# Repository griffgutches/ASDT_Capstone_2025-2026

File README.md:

# ASDT Datalogger
This PCB is a rocketry flight datalogger with a comprehensive sensor suite.

## Features
- GPS
- Radio
- IMU
- Barometer
- Magnetometer
- Status LEDs
- Reverse polarity protection

## Parts
- ESP32-S3 microcontroller
- u-blox MAX-M10S GPS
- RFM95W-915 radio (SX1276)
- ISM6HG256X High/Low-G IMU
- BMI088 Low-G IMU
- ADXL375 High-G IMU
- MS5607 barometer
- BMP390 barometer
- MMC5983MA magnetometer

## Pinout
| GPIO | Function            |
|------|---------------------|
|    0 | BOOT                |
|    1 | MS5607 Baro CS      |
|    2 | BMP390 Baro CS      |
|    4 | MMC598 Mag CS       |
|    7 | Radio CS            |
|   14 | BMI088 Gyro CS      |
|   21 | ADXL375 IMU CS      |
|   40 | BMI088 Accel CS     |
|   41 | ISM6HG256X IMU CS   |
|   11 | ADXL375 INT         |
|   13 | Radio INT           |
|   18 | BMI088 Accel INT    |
|   31 | GPS INT             |
|   42 | MMC598 Mag INT      |
|   10 | MISO                |
|   17 | SCK                 |
|   44 | MOSI                |
|   45 | SCL*                |
|   46 | SDA*                |
|   25 | Flash I03           |
|   26 | Flash I02           |
|   27 | Flash CS            |
|   28 | Flash CLK           |
|   29 | Flash IO1           |
|   30 | Flash IO0           |
|   35 | SD CMD              |
|   37 | SD data 0           |
|   38 | SD data 1           |
|   33 | SD data 2           |
|   34 | SD data 3           |
|   36 | SD clock            |
|   15 | XTAL_32K_P          |
|   16 | XTAL_32K_N          |
|   19 | USB_D-              |
|   20 | USB_D+              |
|    8 | Timepulse           |
|    9 | Battery Sense       |
|   39 | Buzzer              |
|   43 | ANT_SW              |
|    6 | Radio Busy          |

*SDA/SCL should be moved off GPIO45/46 on future designs because they are strapping pins

## Addresses
| Name             | Part     | I2C Address |
|------------------|----------|-------------|
| GPS              | MAX-M10S | 0x42 ****   |

## Notes
- The boot and reset button on the board are enabled by the jumper J5 on the left side of the board, this jumper must be removed before flight
- The radio **may be damaged** if it is run without an antenna attached
- The LED data pin should never be floating
- The battery sense pin is connected through a 300k-100k voltage divider, so the pin voltage is 0.25 times the battery voltage
- The total current consumption should be below 500mA continuous
- The GPS will blink an LED near the bottom of the board once per second once it gets a fix

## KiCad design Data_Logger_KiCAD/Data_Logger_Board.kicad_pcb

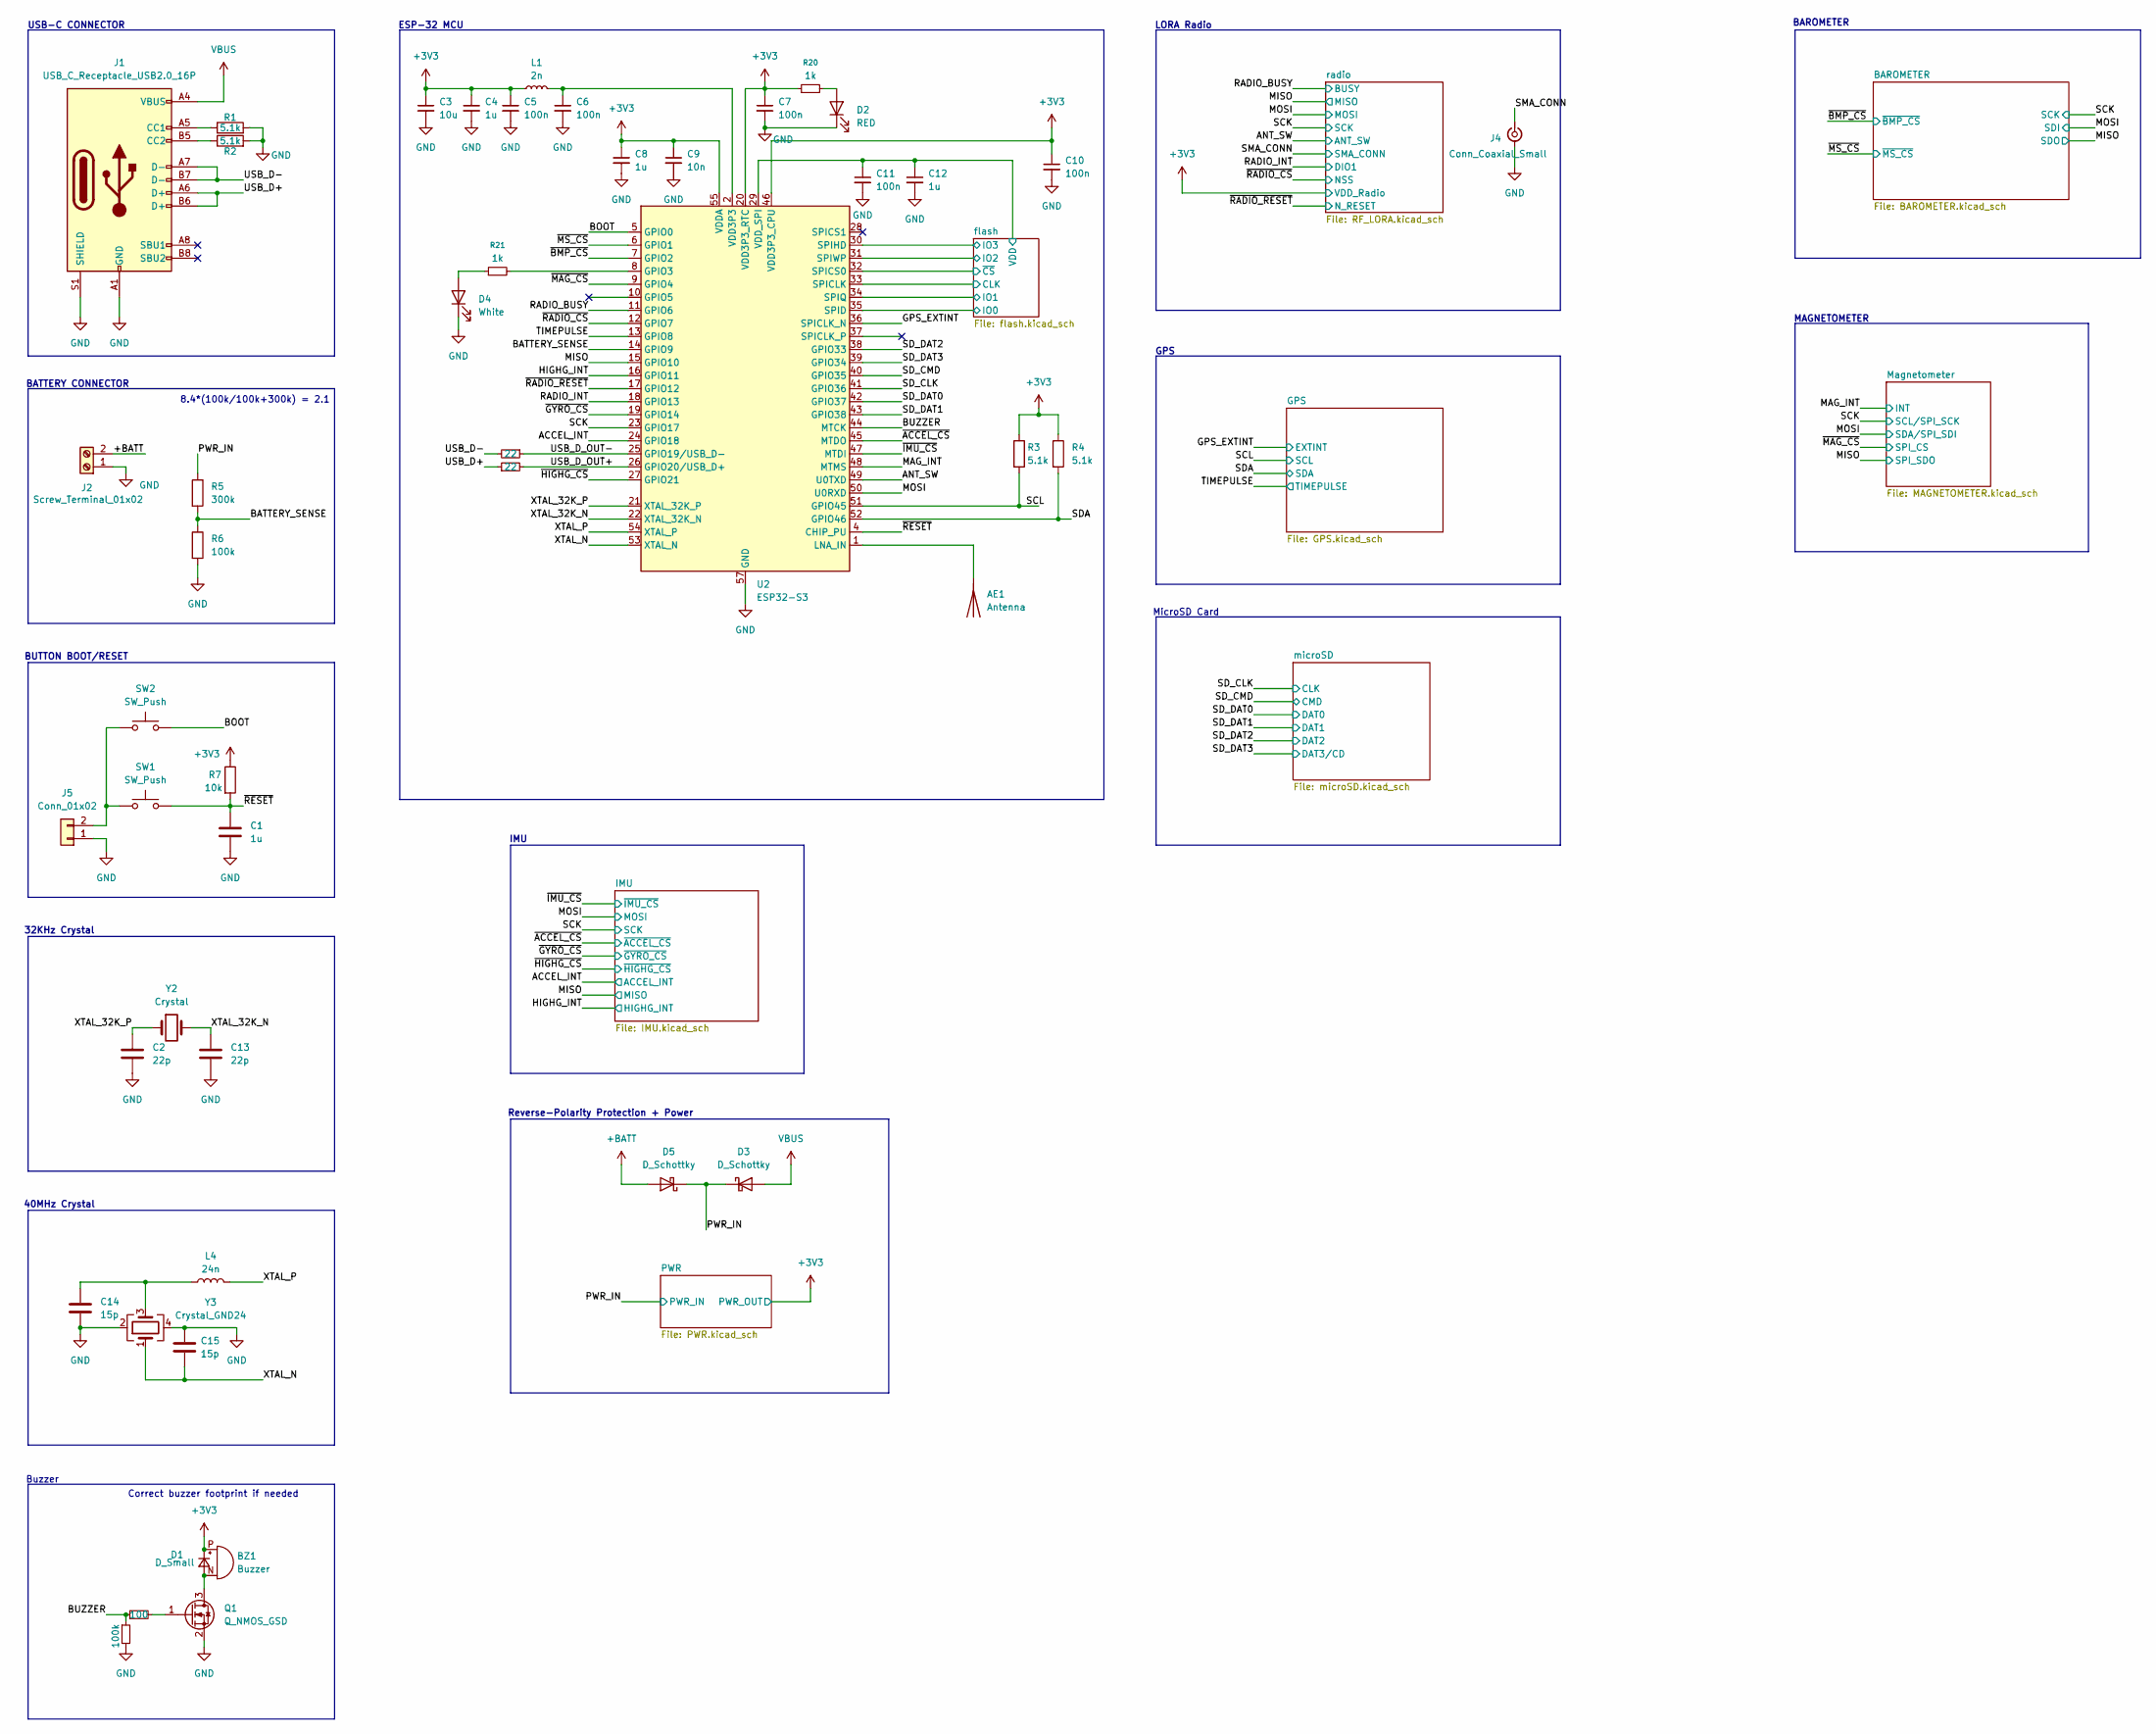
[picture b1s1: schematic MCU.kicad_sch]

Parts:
AE1: Antenna; Molex_47948-0001_2.4Ghz; LCSC C152351
BZ1: Buzzer; CUI_CMT-4023S-SMT-TR
C1, C4, C8, C12: 1u; C_0402_1005Metric; LCSC C52923
C2, C13: 22p; C_0402_1005Metric; LCSC C1555
C3: 10u; C_0603_1608Metric; LCSC C19702
C5, C6, C7, C10, C11: 100n; C_0402_1005Metric; LCSC C1525
C9: 10n; C_0402_1005Metric; LCSC C15195
C14, C15: 15p; C_0402_1005Metric; LCSC C1548
D1: D_Small; D_SOD-123F; LCSC C64898
D2: RED; LED_0603_1608Metric
D3, D5: D_Schottky; D_SOD-123; LCSC C8598
D4: White; LED_0603_1608Metric
J1: USB_C_Receptacle_USB2.0_16P; USB_C_Receptacle_G-Switch_GT-USB-7010ASV; LCSC C2988369
J2: Screw_Terminal_01x02; TerminalBlock_Xinya_XY308-2.54-2P_1x02_P2.54mm_Horizontal
J4: Conn_Coaxial_Small; SMA_Samtec_SMA-J-P-H-ST-EM1_EdgeMount
J5: Conn_01x02; PinHeader_1x02_P1.27mm_Vertical
L1: 2n; L_0402_1005Metric; LCSC C18216
L4: 24n; L_0402_1005Metric; LCSC C74301
Q1: Q_NMOS_GSD; SOT-23; LCSC C28646273
R1, R2, R3, R4: 5.1k; R_0402_1005Metric; LCSC C25905
R5: 300k; R_0402_1005Metric; LCSC C25774
R6, R14: 100k; R_0402_1005Metric; LCSC C25741
R7: 10k; R_0402_1005Metric; LCSC C25744
R11, R12: 22; R_0402_1005Metric; LCSC C25092
R13: 100; R_0402_1005Metric; LCSC C25076
R20, R21: 1k; R_0402_1005Metric; LCSC C11702
SW1, SW2: SW_Push; SW_SPST_TS-1088-xR020; LCSC C720477
U2: ESP32-S3; QFN-56-1EP_7x7mm_P0.4mm_EP4x4mm; LCSC C2913192
Y2: Crystal; Crystal_SMD_3215-2Pin_3.2x1.5mm; LCSC C32346
Y3: Crystal_GND24; Crystal_SMD_2016-4Pin_2.0x1.6mm; LCSC C501798

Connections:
+3V3: BZ1.P (+), C3.1, C4.1, C5.1, C7.1, C8.1, C9.1, C10.1, D1.1 (K), L1.1, R3.1, R4.1, R7.1, R20.1, U2.20 (VDD3P3_RTC), U2.46 (VDD3P3_CPU), U2.55 (VDDA), U2.56 (VDDA); also elsewhere on the board
+BATT: D5.2 (A), J2.2
/MCU/ACCEL_INT: U2.24 (GPIO18); also elsewhere on the board
/MCU/ANT_SW: U2.49 (U0TXD); also elsewhere on the board
/MCU/BATTERY_SENSE: R5.2, R6.1, U2.14 (GPIO9)
/MCU/BOOT: SW2.2, U2.5 (GPIO0)
/MCU/BUZZER: R13.1, R14.1, U2.44 (MTCK)
/MCU/GPS_EXTINT: U2.36 (SPICLK_N); also elsewhere on the board
/MCU/HIGHG_INT: U2.16 (GPIO11); also elsewhere on the board
/MCU/MAG_INT: U2.48 (MTMS); also elsewhere on the board
/MCU/MISO: U2.15 (GPIO10); also elsewhere on the board
/MCU/MOSI: U2.50 (U0RXD); also elsewhere on the board
/MCU/PWR_IN: D3.1 (K), D5.1 (K), R5.1; also elsewhere on the board
/MCU/RADIO_BUSY: U2.11 (GPIO6); also elsewhere on the board
/MCU/RADIO_INT: U2.18 (GPIO13); also elsewhere on the board
/MCU/SCK: U2.23 (GPIO17); also elsewhere on the board
/MCU/SCL: R3.2, U2.51 (GPIO45); also elsewhere on the board
/MCU/SDA: R4.2, U2.52 (GPIO46); also elsewhere on the board
/MCU/SD_CLK: U2.41 (GPIO36); also elsewhere on the board
/MCU/SD_CMD: U2.40 (GPIO35); also elsewhere on the board
/MCU/SD_DAT0: U2.42 (GPIO37); also elsewhere on the board
/MCU/SD_DAT1: U2.43 (GPIO38); also elsewhere on the board
/MCU/SD_DAT2: U2.38 (GPIO33); also elsewhere on the board
/MCU/SD_DAT3: U2.39 (GPIO34); also elsewhere on the board
/MCU/SMA_CONN: J4.1 (In); also elsewhere on the board
/MCU/TIMEPULSE: U2.13 (GPIO8); also elsewhere on the board
/MCU/USB_D+: J1.A6 (D+), J1.B6 (D+), R12.1
/MCU/USB_D-: J1.A7 (D-), J1.B7 (D-), R11.2
/MCU/USB_D_OUT+: R12.2, U2.26 (GPIO20/USB_D+)
/MCU/USB_D_OUT-: R11.1, U2.25 (GPIO19/USB_D-)
/MCU/XTAL_32K_N: C13.1, U2.22 (XTAL_32K_N), Y2.2
/MCU/XTAL_32K_P: C2.1, U2.21 (XTAL_32K_P), Y2.1
/MCU/XTAL_N: C15.2, U2.53 (XTAL_N), Y3.1
/MCU/XTAL_P: L4.2, U2.54 (XTAL_P)
/MCU/flash/CLK: U2.33 (SPICLK); also elsewhere on the board
/MCU/flash/IO0: U2.35 (SPID); also elsewhere on the board
/MCU/flash/IO1: U2.34 (SPIQ); also elsewhere on the board
/MCU/flash/IO2: U2.31 (SPIWP); also elsewhere on the board
/MCU/flash/IO3: U2.30 (SPIHD); also elsewhere on the board
/MCU/flash/VDD: C11.1, C12.1, U2.29 (VDD_SPI); also elsewhere on the board
/MCU/flash/~CS: U2.32 (SPICS0); also elsewhere on the board
/MCU/~ACCEL_CS: U2.45 (MTDO); also elsewhere on the board
/MCU/~BMP_CS: U2.7 (GPIO2); also elsewhere on the board
/MCU/~GYRO_CS: U2.19 (GPIO14); also elsewhere on the board
/MCU/~HIGHG_CS: U2.27 (GPIO21); also elsewhere on the board
/MCU/~IMU_CS: U2.47 (MTDI); also elsewhere on the board
/MCU/~MAG_CS: U2.9 (GPIO4); also elsewhere on the board
/MCU/~MS_CS: U2.6 (GPIO1); also elsewhere on the board
/MCU/~RADIO_CS: U2.12 (GPIO7); also elsewhere on the board
/MCU/~RADIO_RESET: U2.17 (GPIO12); also elsewhere on the board
/MCU/~RESET: C1.1, R7.2, SW1.2, U2.4 (CHIP_PU)
GND: C1.2, C2.2, C3.2, C4.2, C5.2, C6.2, C7.2, C8.2, C9.2, C10.2, C11.2, C12.2, C13.2, C14.2, C15.1, D2.1 (K), D4.1 (K), J1.A1 (GND), J1.A12 (GND), J1.B1 (GND), J1.B12 (GND), J1.S1 (SHIELD), J2.1, J4.2 (Ext), J5.1, Q1.2 (S), R1.2, R2.2, R6.2, R14.2, U2.57 (GND), Y3.2, Y3.4; also elsewhere on the board
unnamed: AE1.1 (A), U2.1 (LNA_IN)
unnamed: BZ1.N (-), D1.2 (A), Q1.3 (D)
unnamed: C6.1, L1.2, U2.2 (VDD3P3), U2.3 (VDD3P3)
unnamed: C14.1, L4.1, Y3.3
unnamed: D2.2 (A), R20.2
unnamed: D4.2 (A), R21.1
unnamed: J1.A5 (CC1), R1.1
unnamed: J1.B5 (CC2), R2.1
unnamed: J5.2, SW1.1, SW2.1
unnamed: Q1.1 (G), R13.2
unnamed: R21.2, U2.8 (GPIO3)
VBUS: D3.2 (A), J1.A4 (VBUS), J1.A9 (VBUS), J1.B4 (VBUS), J1.B9 (VBUS)

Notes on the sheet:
ESP-32 MCU
Correct buzzer footprint if needed
Buzzer
MAGNETOMETER
Reverse-Polarity Protection + Power
IMU
BATTERY CONNECTOR
BUTTON BOOT/RESET
MicroSD Card
8.4*(100k/100k+300k) = 2.1
32KHz Crystal
40MHz Crystal
BAROMETER
LORA Radio
GPS
USB-C CONNECTOR

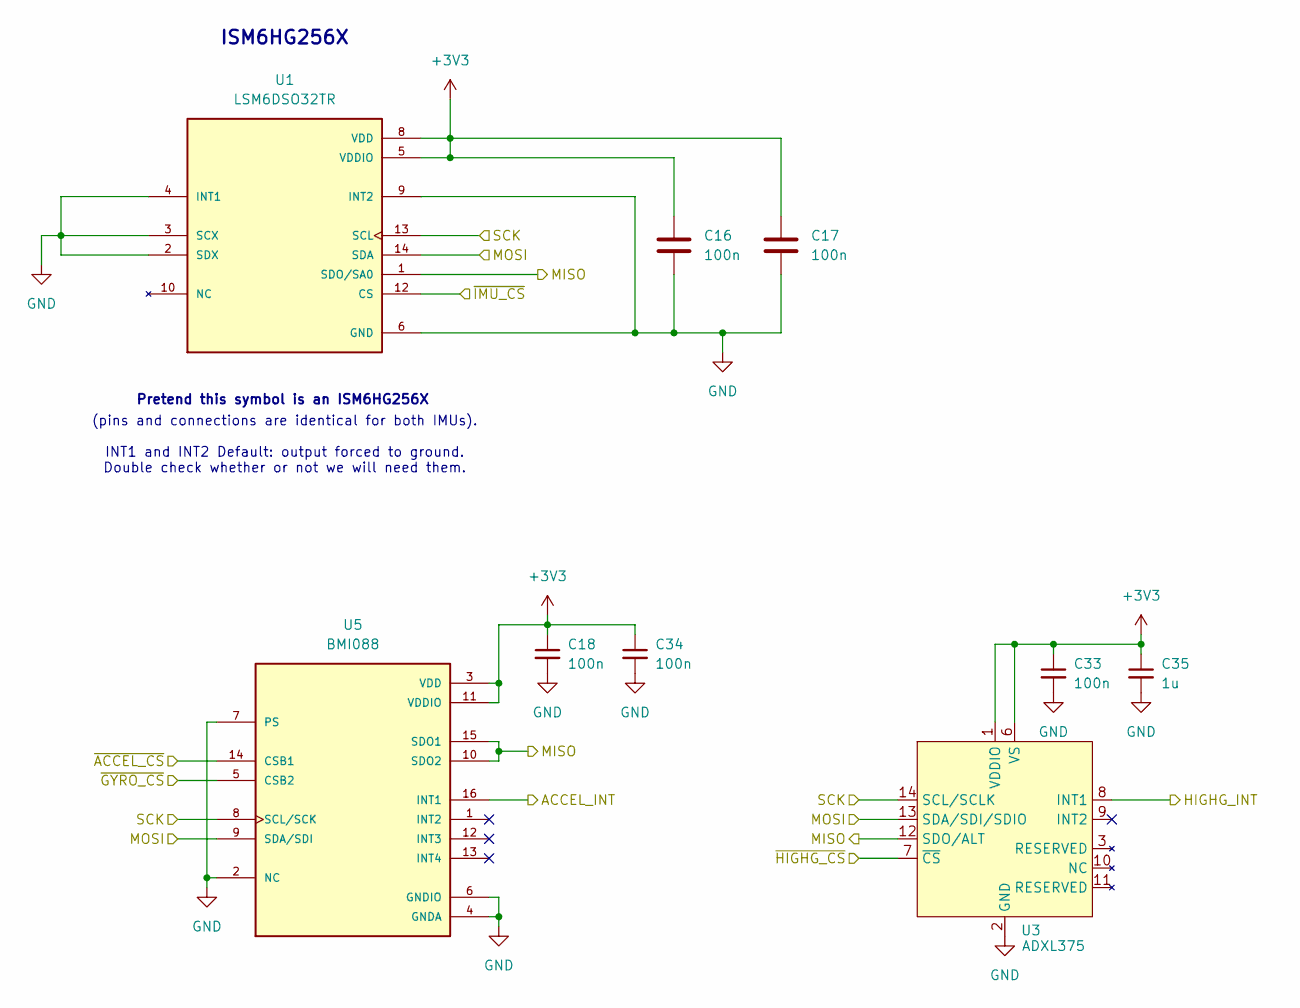
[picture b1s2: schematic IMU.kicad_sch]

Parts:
C16, C17, C18, C33, C34: 100n; C_0402_1005Metric; LCSC C1525
C35: 1u; C_0402_1005Metric; LCSC C52923
U1: LSM6DSO32TR; LGA-14_3x2.5mm_P0.5mm_LayoutBorder3x4y; PARTREV 1
U3: ADXL375; LGA_CC-14-1_ADI; digikey ADXL375BCCZ-RL7CT-ND
U5: BMI088; PQFN50P450X300X100-16N

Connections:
+3V3: C16.1, C17.1, C18.1, C33.1, C34.1, C35.1, U1.5 (VDDIO), U1.8 (VDD), U3.1 (VDDIO), U3.6 (VS), U5.3 (VDD), U5.11 (VDDIO); also elsewhere on the board
/MCU/ACCEL_INT: U5.16 (INT1); also elsewhere on the board
/MCU/HIGHG_INT: U3.8 (INT1); also elsewhere on the board
/MCU/MISO: U1.1 (SDO/SA0), U3.12 (SDO/ALT), U5.10 (SDO2), U5.15 (SDO1); also elsewhere on the board
/MCU/MOSI: U1.14 (SDA), U3.13 (SDA/SDI/SDIO), U5.9 (SDA/SDI); also elsewhere on the board
/MCU/SCK: U1.13 (SCL), U3.14 (SCL/SCLK), U5.8 (SCL/SCK); also elsewhere on the board
/MCU/~ACCEL_CS: U5.14 (CSB1); also elsewhere on the board
/MCU/~GYRO_CS: U5.5 (CSB2); also elsewhere on the board
/MCU/~HIGHG_CS: U3.7 (~CS); also elsewhere on the board
/MCU/~IMU_CS: U1.12 (CS); also elsewhere on the board
GND: C16.2, C17.2, C18.2, C33.2, C34.2, C35.2, U1.2 (SDX), U1.3 (SCX), U1.4 (INT1), U1.6 (GND), U1.7 (GND), U1.9 (INT2), U3.2 (GND), U3.4 (GND), U3.5 (GND), U5.2 (NC), U5.4 (GNDA), U5.6 (GNDIO), U5.7 (PS); also elsewhere on the board

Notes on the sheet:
Pretend this symbol is an ISM6HG256X
ISM6HG256X
(pins and connections are identical for both IMUs). INT1 and INT2 Default: output forced to ground. Double check whether or not we will need them.

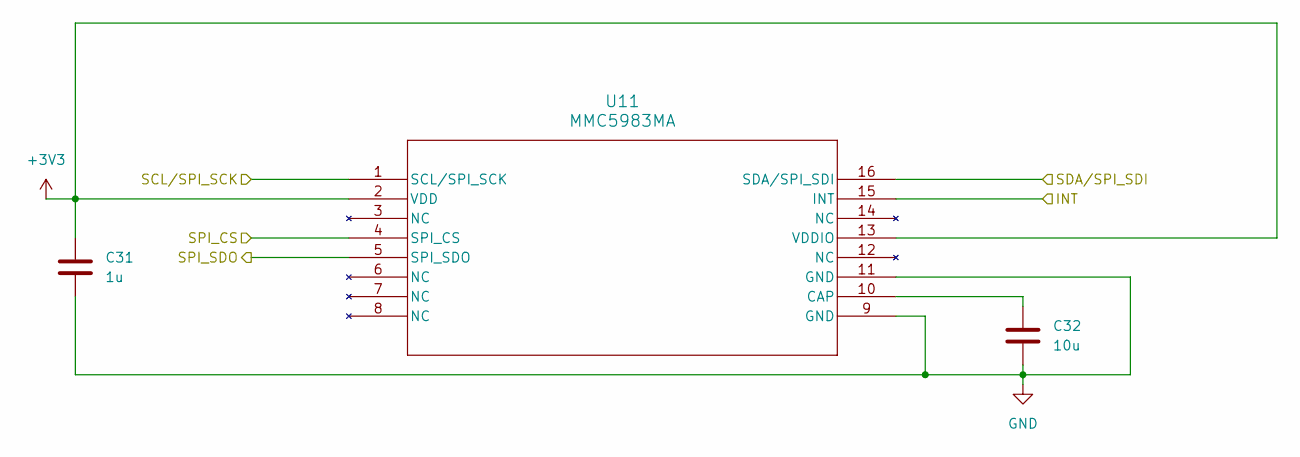
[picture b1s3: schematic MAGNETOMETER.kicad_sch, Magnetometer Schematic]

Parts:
C31: 1u; C_0402_1005Metric; LCSC C52923
C32: 10u; C_0402_1005Metric; LCSC C15525
U11: MMC5983MA; LGA-16_3x3mm_P0.5mm_LayoutBorder3x5y

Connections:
+3V3: C31.1, U11.2 (VDD), U11.13 (VDDIO); also elsewhere on the board
/MCU/MAG_INT: U11.15 (INT); also elsewhere on the board
/MCU/MISO: U11.5 (SPI_SDO); also elsewhere on the board
/MCU/MOSI: U11.16 (SDA/SPI_SDI); also elsewhere on the board
/MCU/SCK: U11.1 (SCL/SPI_SCK); also elsewhere on the board
/MCU/~MAG_CS: U11.4 (SPI_CS); also elsewhere on the board
GND: C31.2, C32.2, U11.9 (GND), U11.11 (GND); also elsewhere on the board
unnamed: C32.1, U11.10 (CAP)

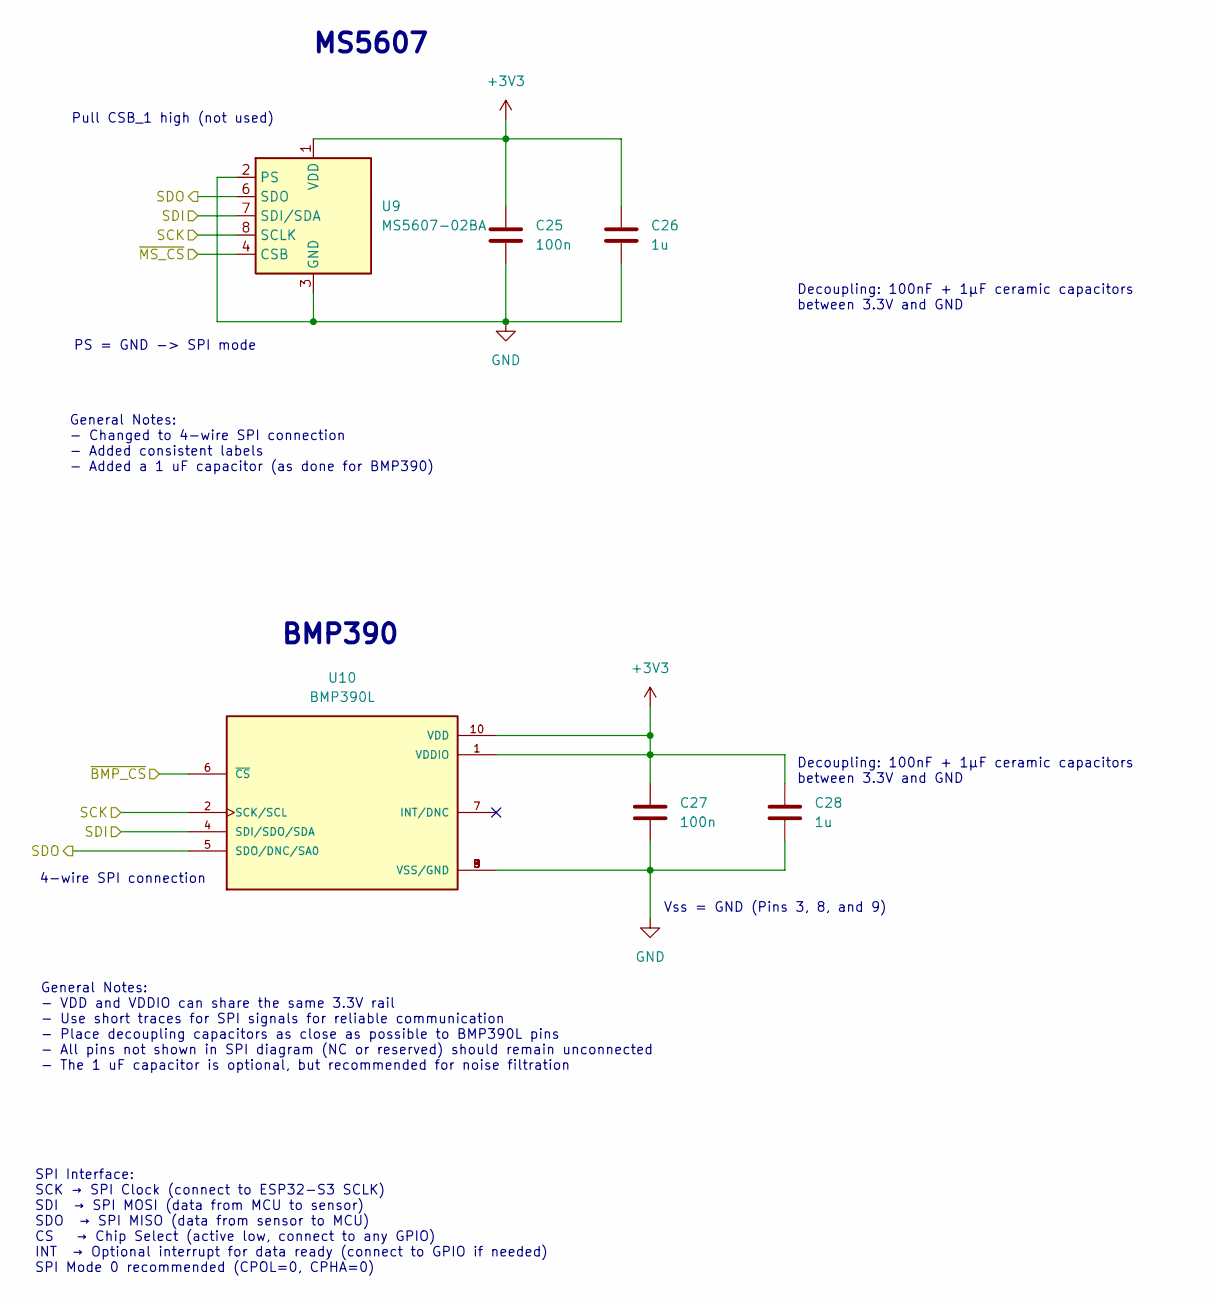
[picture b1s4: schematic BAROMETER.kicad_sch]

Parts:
C25, C27: 100n; C_0402_1005Metric; LCSC C1525
C26, C28: 1u; C_0402_1005Metric; LCSC C52923
U9: MS5607-02BA; LGA-8_3x5mm_P1.25mm; LCSC C97627
U10: BMP390L; XDCR_BMP390L; PARTREV 1.7

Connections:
+3V3: C25.1, C26.2, C27.1, C28.1, U9.1 (VDD), U10.1 (VDDIO), U10.10 (VDD); also elsewhere on the board
/MCU/MISO: U9.6 (SDO), U10.5 (SDO/DNC/SA0); also elsewhere on the board
/MCU/MOSI: U9.7 (SDI/SDA), U10.4 (SDI/SDO/SDA); also elsewhere on the board
/MCU/SCK: U9.8 (SCLK), U10.2 (SCK/SCL); also elsewhere on the board
/MCU/~BMP_CS: U10.6 (~CS); also elsewhere on the board
/MCU/~MS_CS: U9.4 (CSB), U9.5 (CSB); also elsewhere on the board
GND: C25.2, C26.1, C27.2, C28.2, U9.2 (PS), U9.3 (GND), U10.3 (VSS/GND), U10.8 (VSS/GND), U10.9 (VSS/GND); also elsewhere on the board

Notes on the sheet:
4-wire SPI connection
Decoupling: 100nF + 1µF ceramic capacitors between 3.3V and GND
Vss = GND (Pins 3, 8, and 9)
MS5607
General Notes: - Changed to 4-wire SPI connection - Added consistent labels - Added a 1 uF capacitor (as done for BMP390)
BMP390
PS = GND -> SPI mode
Pull CSB_1 high (not used)
SPI Interface: SCK → SPI Clock (connect to ESP32-S3 SCLK) SDI → SPI MOSI (data from MCU to sensor) SDO → SPI MISO (data from sensor to MCU) CS → Chip Select (active low, connect to any GPIO) INT → Optional interrupt for data ready (connect to GPIO if needed) SPI Mode 0 recommended (CPOL=0, CPHA=0)
General Notes: - VDD and VDDIO can share the same 3.3V rail - Use short traces for SPI signals for reliable communication - Place decoupling capacitors as close as possible to BMP390L pins - All pins not shown in SPI diagram (NC or reserved) should remain unconnected - The 1 uF capacitor is optiona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

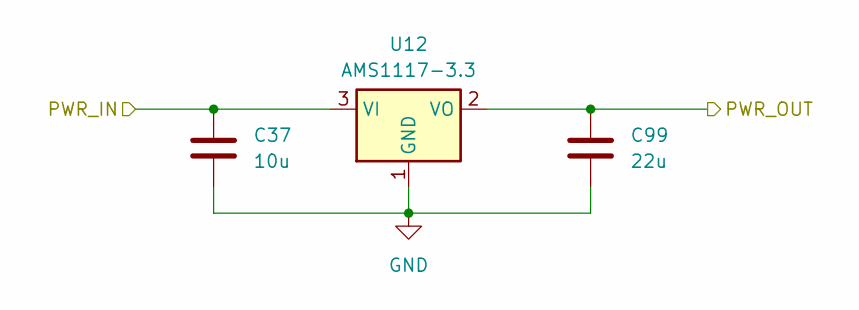
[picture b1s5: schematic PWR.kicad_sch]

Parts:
C37: 10u; C_0603_1608Metric; LCSC C19702
C99: 22u; C_0603_1608Metric; LCSC C59461
U12: AMS1117-3.3; SOT-223-3_TabPin2; LCSC C6186

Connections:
+3V3: C99.1, U12.2 (VO); also elsewhere on the board
/MCU/PWR_IN: C37.1, U12.3 (VI); also elsewhere on the board
GND: C37.2, C99.2, U12.1 (GND); also elsewhere on the board

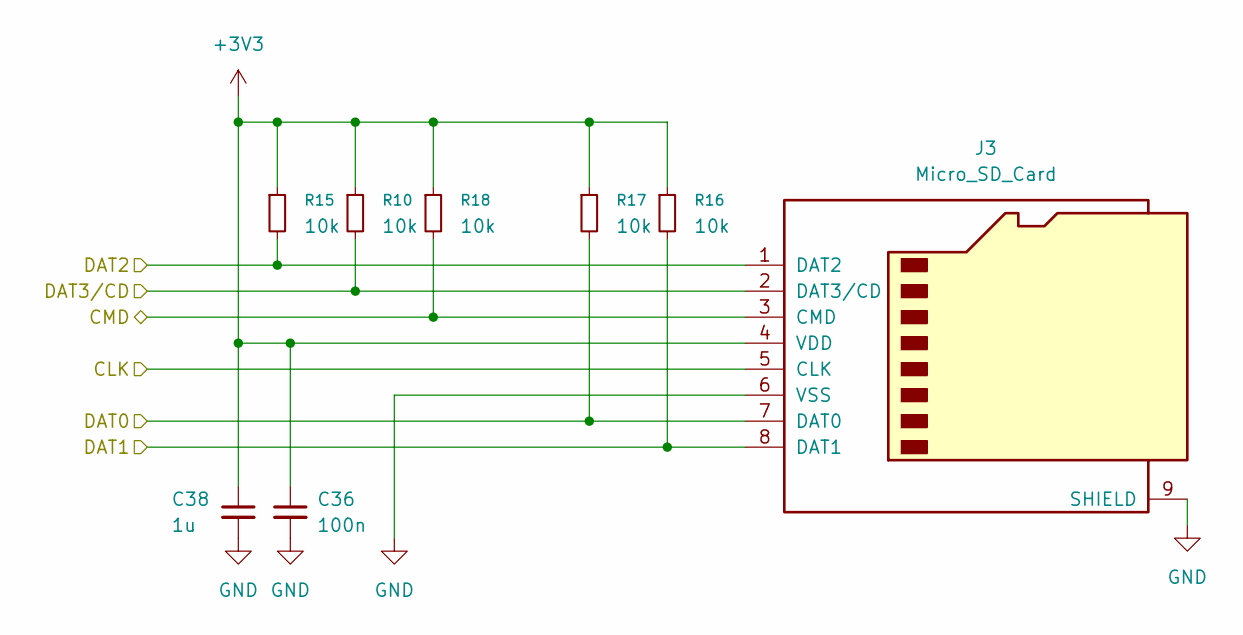
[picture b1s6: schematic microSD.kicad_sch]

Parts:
C36: 100n; C_0402_1005Metric; LCSC C1525
C38: 1u; C_0402_1005Metric; LCSC C52923
J3: Micro_SD_Card; microSD_HC_Molex_47219-2001; LCSC C164170
R10, R15, R16, R17, R18: 10k; R_0402_1005Metric; LCSC C25744

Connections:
+3V3: C36.1, C38.1, J3.4 (VDD), R10.1, R15.1, R16.1, R17.1, R18.1; also elsewhere on the board
/MCU/SD_CLK: J3.5 (CLK); also elsewhere on the board
/MCU/SD_CMD: J3.3 (CMD), R18.2; also elsewhere on the board
/MCU/SD_DAT0: J3.7 (DAT0), R17.2; also elsewhere on the board
/MCU/SD_DAT1: J3.8 (DAT1), R16.2; also elsewhere on the board
/MCU/SD_DAT2: J3.1 (DAT2), R15.2; also elsewhere on the board
/MCU/SD_DAT3: J3.2 (DAT3/CD), R10.2; also elsewhere on the board
GND: C36.2, C38.2, J3.6 (VSS), J3.9 (SHIELD); also elsewhere on the board

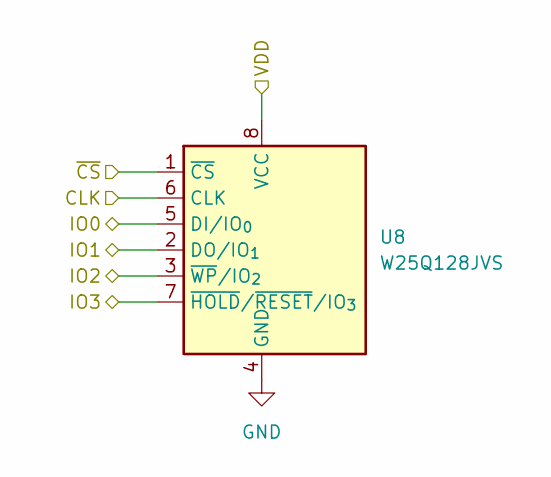
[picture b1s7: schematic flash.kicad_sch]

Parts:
U8: W25Q128JVS; SOIC-8_5.3x5.3mm_P1.27mm; LCSC C97521

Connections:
/MCU/flash/CLK: U8.6 (CLK); also elsewhere on the board
/MCU/flash/IO0: U8.5 (DI/IO_{0}); also elsewhere on the board
/MCU/flash/IO1: U8.2 (DO/IO_{1}); also elsewhere on the board
/MCU/flash/IO2: U8.3 (~WP/IO_{2}); also elsewhere on the board
/MCU/flash/IO3: U8.7 (~HOLD/~RESET/IO_{3}); also elsewhere on the board
/MCU/flash/VDD: U8.8 (VCC); also elsewhere on the board
/MCU/flash/~CS: U8.1 (~CS); also elsewhere on the board
GND: U8.4 (GND); also elsewhere on the board

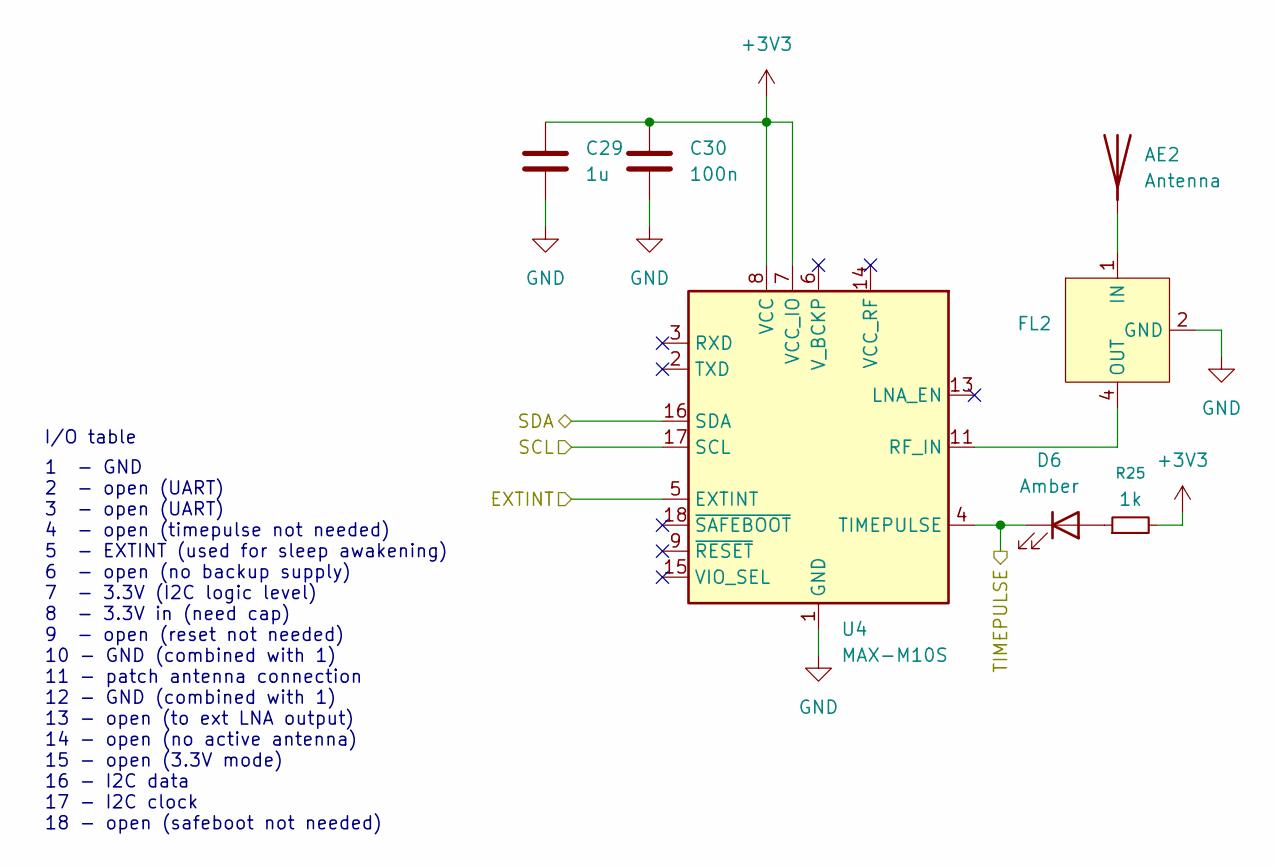
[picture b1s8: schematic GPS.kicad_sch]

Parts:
AE2: Antenna; YG0043AA
C29: 1u; C_0402_1005Metric; LCSC C52923
C30: 100n; C_0402_1005Metric; LCSC C1525
D6: Amber; LED_0603_1608Metric
FL2: Filter_SAFEA1GXXKA0F00; LCSC C91641
R25: 1k; R_0402_1005Metric; LCSC C11702
U4: MAX-M10S; ublox_MAX

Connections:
+3V3: C29.1, C30.1, R25.2, U4.7 (VCC_IO), U4.8 (VCC); also elsewhere on the board
/MCU/GPS_EXTINT: U4.5 (EXTINT); also elsewhere on the board
/MCU/SCL: U4.17 (SCL); also elsewhere on the board
/MCU/SDA: U4.16 (SDA); also elsewhere on the board
/MCU/TIMEPULSE: D6.1 (K), U4.4 (TIMEPULSE); also elsewhere on the board
GND: C29.2, C30.2, FL2.2 (GND), FL2.3 (GND), FL2.5 (GND), U4.1 (GND), U4.10 (GND), U4.12 (GND); also elsewhere on the board
unnamed: AE2.1 (A), FL2.1 (IN)
unnamed: D6.2 (A), R25.1
unnamed: FL2.4 (OUT), U4.11 (RF_IN)

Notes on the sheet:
1 - GND 2 - open (UART) 3 - open (UART) 4 - open (timepulse not needed) 5 - EXTINT (used for sleep awakening) 6 - open (no backup supply) 7 - 3.3V (I2C logic level) 8 - 3.3V in (need cap) 9 - open (reset not needed) 10 - GND (combined with 1) 11 - patch antenna connection 12 - GND (combined with 1)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
I/O table

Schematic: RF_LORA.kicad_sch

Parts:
C19: 100n; C_0402_1005Metric; LCSC C1525
C20: 1u; C_0402_1005Metric; LCSC C52923
C21: 47n; C_0603_1608Metric; LCSC C1622
C22: 47p; C_0402_1005Metric; LCSC C1567
C23, C24, C41, C42, C43: 1n; C_0402_1005Metric; LCSC C1523
C39: 10n; C_0402_1005Metric; LCSC C15195
C40: 10p; C_0402_1005Metric; LCSC C32949
FB1: FerriteBead_Small; L_0603_1608Metric; LCSC C14709
FL1: 0900FM15K0039; Balun_Johanson_0900FM15K0039
L2, L3: 47n; L_0402_1005Metric; LCSC C27151
R8, R9: 100; R_0402_1005Metric; LCSC C25076
R19: 220; R_0402_1005Metric; LCSC C25091
U6: SX1262IMLTRT; QFN-24-1EP_4x4mm_P0.5mm_EP2.6x2.6mm
U7: MASW-007221; SOT-363_SC-70-6
XTAL3: NT2016SA-32M-END4263A; NT2016SA-32M-END4263A_NDK; LCSC C36338880

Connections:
+3V3: FB1.2; also elsewhere on the board
/MCU/ANT_SW: R9.1; also elsewhere on the board
/MCU/MISO: U6.16 (MISO); also elsewhere on the board
/MCU/MOSI: U6.17 (MOSI); also elsewhere on the board
/MCU/RADIO_BUSY: U6.14 (BUSY); also elsewhere on the board
/MCU/RADIO_INT: U6.13 (DIO1); also elsewhere on the board
/MCU/SCK: U6.18 (SCK); also elsewhere on the board
/MCU/SMA_CONN: C41.2; also elsewhere on the board
/MCU/radio/DIO2: R8.1, U6.12 (DIO2)
/MCU/radio/TCXO_VCC: C39.1, U6.6 (DIO3), XTAL3.4 (VCC)
/MCU/radio/XTA: R19.2, U6.3 (XTA)
/MCU/~RADIO_CS: U6.19 (NSS); also elsewhere on the board
/MCU/~RADIO_RESET: U6.15 (~RESET); also elsewhere on the board
GND: C19.2, C20.1, C21.2, C22.2, C23.2, C24.2, C39.2, FL1.2 (GND), FL1.5 (GND), FL1.7 (GND), FL1.9 (GND), FL1.10 (GND), U6.2 (GND), U6.5 (GND), U6.8 (GND), U6.20 (GND), U6.25 (GND), U7.2 (GND), XTAL3.1 (GND), XTAL3.2 (GND); also elsewhere on the board
unnamed: C40.2, R19.1
unnamed: FL1.3 (RFI_N), U6.22 (RFI_N)
unnamed: FL1.4 (RFI_P), U6.21 (RFI_P)
unnamed: FL1.1 (RFO), L3.2, U6.23 (RFO)
unnamed: C42.1, FL1.6 (SW_RFI)
unnamed: C43.1, FL1.8 (SW_RFO)
unnamed: L2.1, U6.9 (DCC_SW)
unnamed: C19.1, FB1.1, U6.1 (VDD_IN), U6.10 (VBAT), U6.11 (VBAT_IO)
unnamed: C20.2, L2.2, U6.7 (VREG)
unnamed: C21.1, C22.1, L3.1, U6.24 (VR_PA)
unnamed: C43.2, U7.1 (RF1)
unnamed: C42.2, U7.3 (RF2)
unnamed: C41.1, U7.5 (RFC)
unnamed: C23.1, R8.2, U7.6 (V1)
unnamed: C24.1, R9.2, U7.4 (V2)
unnamed: C40.1, XTAL3.3 (OUT)

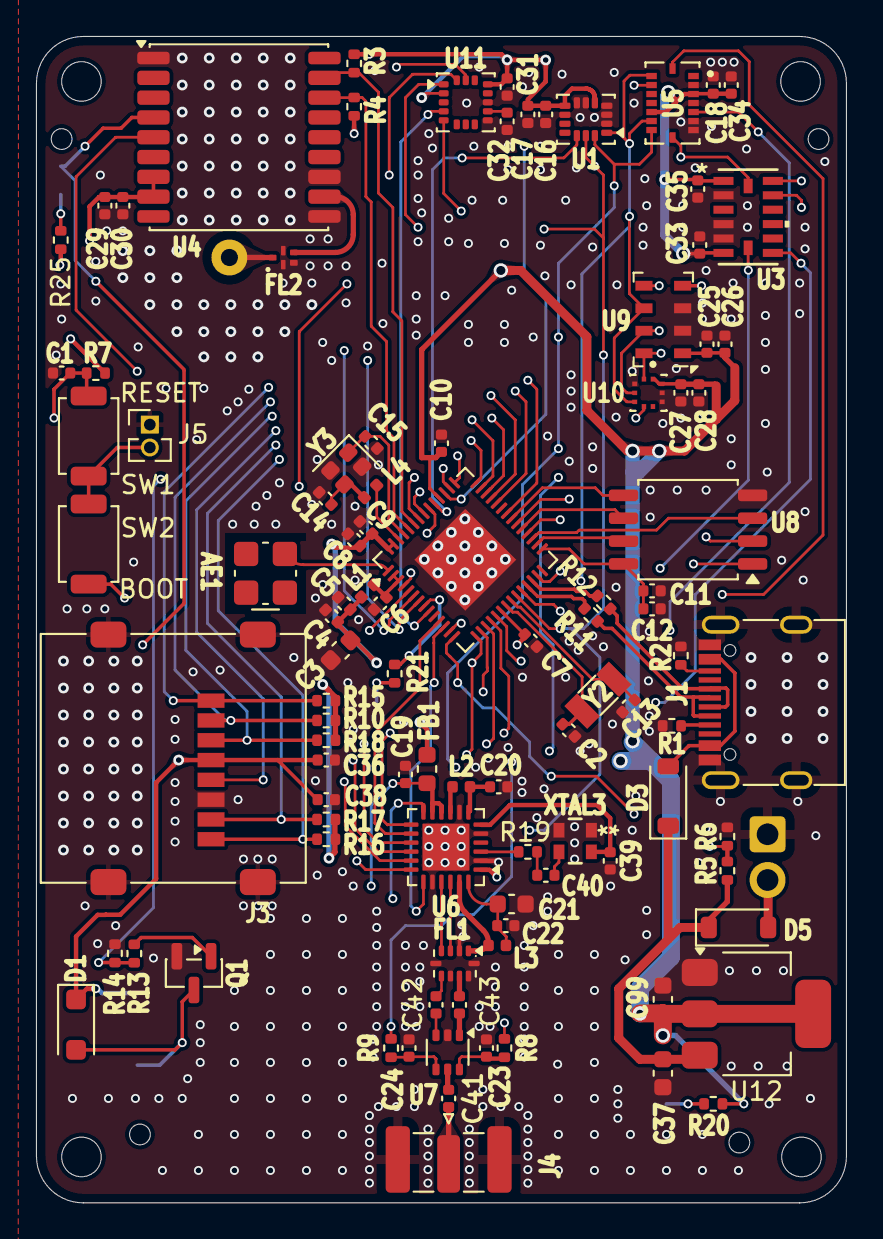
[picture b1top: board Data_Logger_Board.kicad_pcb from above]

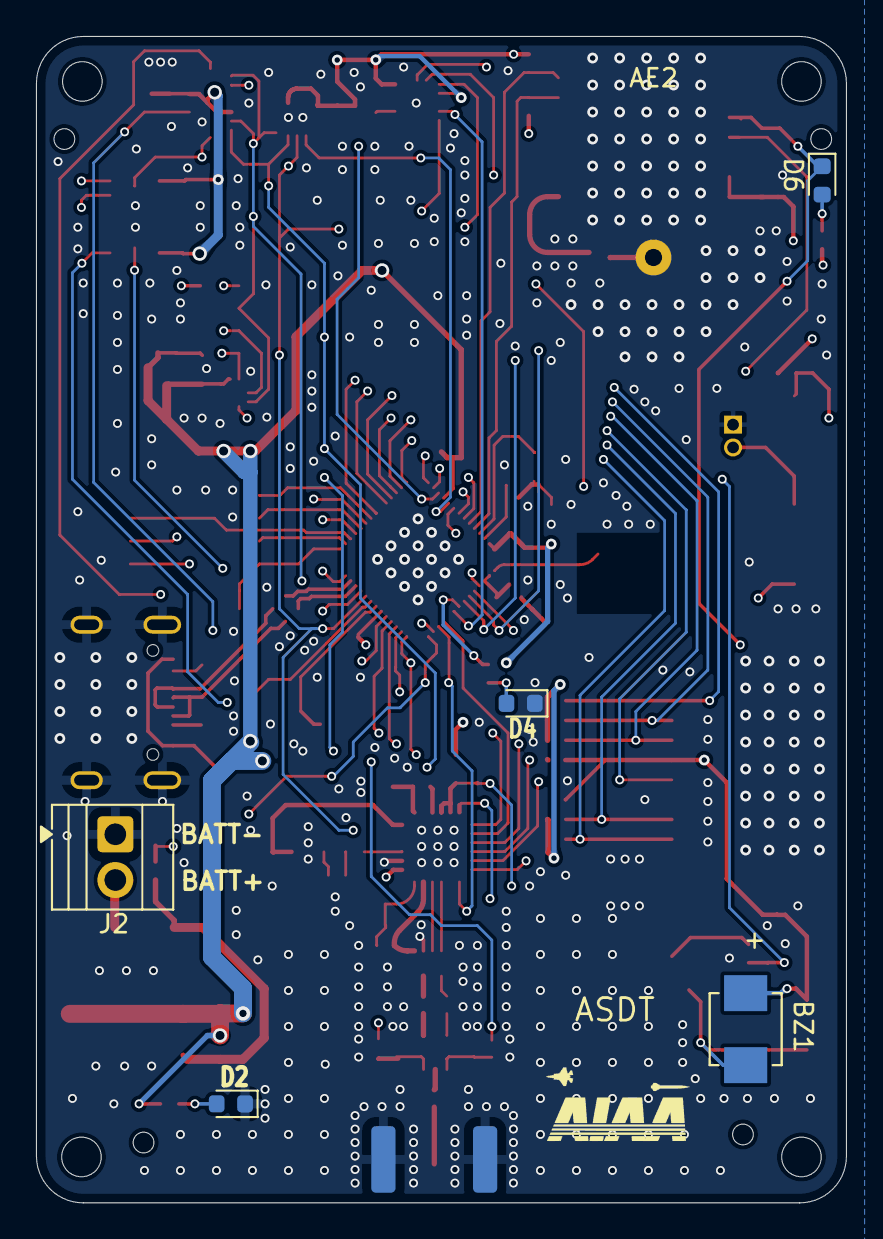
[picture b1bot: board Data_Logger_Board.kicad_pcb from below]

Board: 4 copper layers, 45.0 x 64.8 mm, 109 parts (6 on the bottom side), 87 nets.

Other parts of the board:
H1, H2, H3, H4: MountingHole; MountingHole_2.2mm_M2
